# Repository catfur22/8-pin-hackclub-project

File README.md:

# 8-pin-hackclub-project

# ResistorIQ

ResistorIQ is a resistor tester I'm making for the Hack Club 8-Pin Grant.

The idea is to plug in a resistor, select one of four reference resistors using the rotary switch, and have the device measure its resistance. The result will show up on a 16x2 LCD.

I'm using an ATtiny412 microcontroller and designing the PCB in KiCad. The board has two layers and includes the measurement circuit, rotary switch, and connectors.

I've finished the schematic and PCB layout and generated the manufacturing files. Next I need to get the board made, put everything together, program the microcontroller, and test it.

I'll keep updating this repository as the project progresses.

## KICANVAS LINKS:

https://kicanvas.org/?repo=https%3A%2F%2Fgithub.com%2Fcatfur22%2F8-pin-hackclub-project%2Ftree%2Fmain%2Fhardware%2FResistorIQ

https://kicanvas.org/?repo=https%3A%2F%2Fgithub.com%2Fcatfur22%2F8-pin-hackclub-project%2Fblob%2Fmain%2Fhardware%2FResistorIQ%2Fsimplepcb.kicad_sch

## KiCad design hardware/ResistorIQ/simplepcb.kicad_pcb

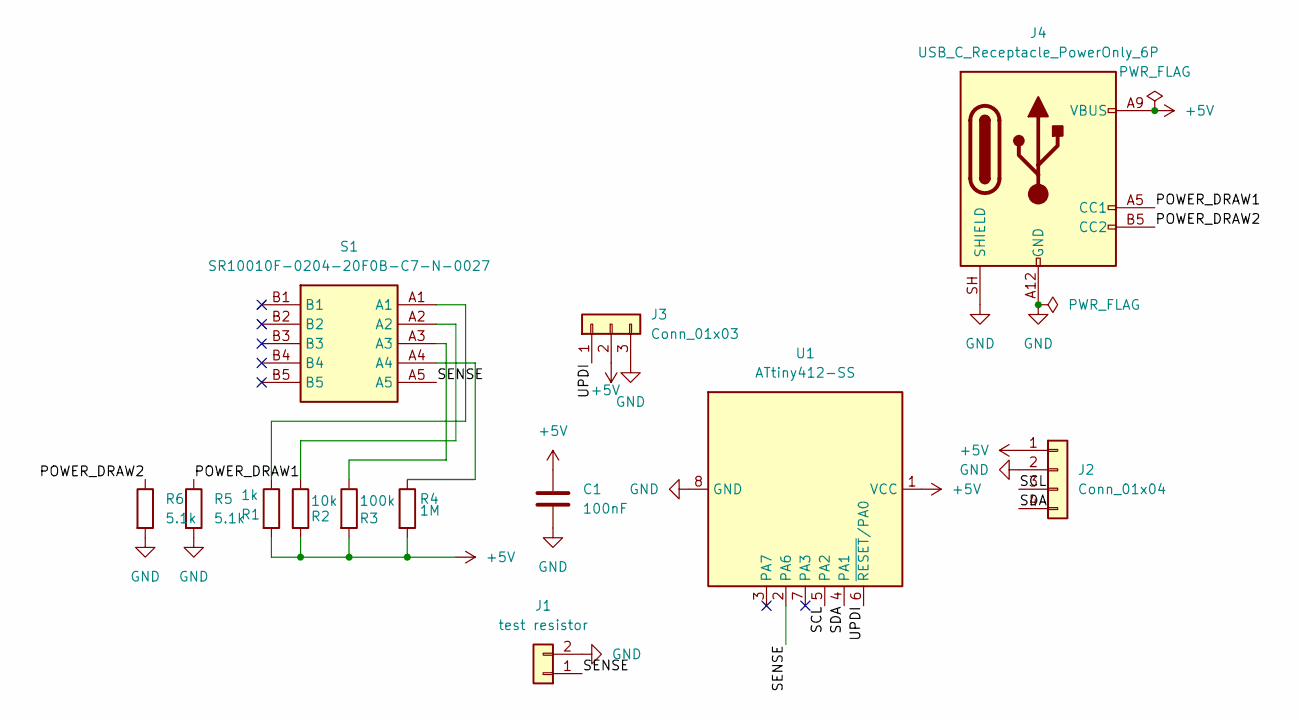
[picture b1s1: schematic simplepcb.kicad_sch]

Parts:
C1: 100nF; C_0805_2012Metric
J1: test resistor; PinSocket_1x02_P2.54mm_Vertical
J2: Conn_01x04; PinSocket_1x04_P2.54mm_Horizontal
J3: Conn_01x03; PinHeader_1x03_P2.54mm_Vertical
J4: USB_C_Receptacle_PowerOnly_6P; USB_C_Receptacle_GCT_USB4085
R1: 1k; R_0805_2012Metric
R2: 10k; R_0805_2012Metric
R3: 100k; R_0805_2012Metric
R4: 1M; R_0805_2012Metric
R5, R6: 5.1k; R_0805_2012Metric
S1: SR10010F-0204-20F0B-C7-N-0027; SR10010F020420F0BC7N0027; Mouser Part Number 105-SR10010F-24NS
U1: ATtiny412-SS; SOIC-8_3.9x4.9mm_P1.27mm

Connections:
+5V: C1.1, J2.1, J3.2, J4.A9 (VBUS), J4.B9 (VBUS), R1.2, R2.2, R3.2, R4.2, U1.1 (VCC)
/POWER_DRAW1: J4.A5 (CC1), R5.1
/POWER_DRAW2: J4.B5 (CC2), R6.1
/SCL: J2.3, U1.5 (PA2)
/SDA: J2.4, U1.4 (PA1)
/SENSE: J1.1, S1.A5, U1.2 (PA6)
/UPDI: J3.1, U1.6 (~RESET/PA0)
GND: C1.2, J1.2, J2.2, J3.3, J4.A12 (GND), J4.B12 (GND), J4.SH (SHIELD), R5.2, R6.2, U1.8 (GND)
unnamed: R1.1, S1.A1
unnamed: R2.1, S1.A2
unnamed: R3.1, S1.A3
unnamed: R4.1, S1.A4

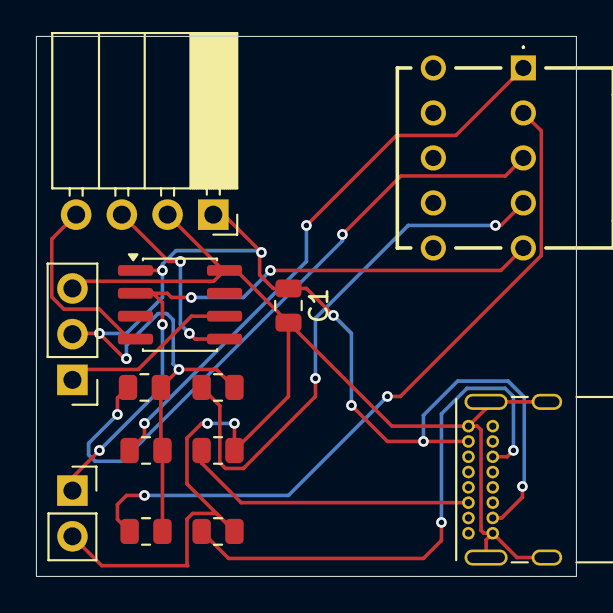
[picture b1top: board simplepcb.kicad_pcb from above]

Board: 2 copper layers, 30.0 x 30.0 mm, 13 parts (0 on the bottom side), 12 nets.
